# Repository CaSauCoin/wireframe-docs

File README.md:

# WireFrame EDA — User Guide

The WireFrame user guide: installation, tutorials, schematic, PCB layout, high-speed and power integrity, simulation, the AI Copilot, libraries, multi-board products, import/export, and reference pages. Published at **<https://wireframe.com.vn/docs/>** (the app's **Help → Documentation**).

This repository holds the **content** — Markdown, the media WireFrame records of itself, and the capture briefs. The pages are drawn by the website, [`wireframe-auth`](../wireframe-auth), with its own header, footer, theme and search (`app/docs_site.py`). Until October 2026 the guide was a separate MkDocs site; it is now one site with wireframe.com.vn, at the same URLs.

```mermaid
flowchart LR
    A[docs/**/*.md + guide.yml] -->|wireframe-auth/app/docs_site.py| B[Static pages at /docs/]
    C[doc_builder captures from the app] --> A
    B --> D[Cloudflare edge, with the website]
```

## Read it while you write it

From the `wireframe-auth` checkout next to this one:

```bash
python main.py                      # http://127.0.0.1:8000/docs/ — rendered on request from this repo
python scripts/build_docs.py build/docs-site --strict   # the static build the deploy makes; fails on a broken link
```

`WF_DOCS_DIR=/path/to/wireframe-docs` points the site at a checkout somewhere else. The deploy (`scripts/build_worker.py`) builds the guide on every Worker build.

## Layout

| Path | Purpose |
|---|---|
| `guide.yml` | The order of the guide (sections and pages) and the words on its home page |
| `docs/**/*.md` | The pages. A page's URL is its path: `docs/pcb/routing.md` → `/docs/pcb/routing/` |
| `docs/assets/wf/` | Screenshots and clips captured by WireFrame's `doc_builder` (with a manifest) |
| `docs/assets/app/` | Pictures drawn by the app's own lab tools (`wf-panel-shot`) — see `docs/assets/app/README.md` |
| `.wf-docs.yaml` | Per-scene settings for `doc_builder` (sample files, hints, skipped scenes) |
| `boards.yaml` | The real open-hardware boards the media is recorded on |
| `samples/` | Sample projects used by capture scenes |

## Writing a page

- Front matter: `description:` (the search snippet, 50–300 characters). Optional `status: new|beta`.
- Markdown with admonitions (`!!! note`), collapsible blocks (`??? question`), tabs (`=== "Tab"`), keys (`++ctrl+s++`), tables, definition lists and code blocks.
- Link pages by their relative `.md` path; the build turns them into URLs and fails on a missing one.
- Name the app's menus and buttons exactly as the app spells them. A page that promises a button the app does not have is worse than no page.
- Add the page to a section in `guide.yml`, or it is not published.

## Images and videos

Sections titled `### Image — …`, `### Short video — …` or `### Diagram — …` are capture slots. Each carries a brief (`!!! note "… brief"`) and, once captured, the media. The website hides the briefs and turns a captured slot into a figure; a slot without media is left out until it is captured. Capture with WireFrame's `doc_builder`:

```bash
python3 -m doc_builder docs-scan ../wireframe-docs
python3 -m doc_builder docs-fill ../wireframe-docs
```

Every picture is drawn by the app itself, on the boards in `boards.yaml` — never mocked up, never the 7805 test project.

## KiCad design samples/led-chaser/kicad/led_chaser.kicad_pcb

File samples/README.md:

# Sample data for documentation captures

Input files used when WireFrame's `doc_builder` lab captures the screenshots
and short videos in this guide (`python3 -m doc_builder docs-fill ../wireframe-docs`
from the WireFrame repository; see `.wf-docs.yaml`).

Everything here is **fictional** and made for this documentation — no
third-party data, no customer data. Regenerate with:

```bash
python3 samples/generate.py      # needs pdftoppm (poppler-utils) for the PNG
```

| File | What it is |
|---|---|
| `outlines/demo-board.dxf` | 80 × 60 mm board, R3 corners, four M3 holes 4 mm from each corner, a 20 × 12 mm battery pocket. ASCII DXF in millimetres |
| `outlines/demo-board.svg` | The same board as SVG (mm) |
| `datasheets/wf-demo8.pdf` | Two-page datasheet of **WF-DEMO8**, a fictional 8-pin SOIC-8 buck converter: pinout, operating conditions, application notes, package data |
| `datasheets/wf-demo8-pinout.png` | The pin table as an image, for the pin-OCR scene |
| `led-chaser/` | The [tutorial](../docs/tutorial/index.md) board — see below |

## The tutorial board: `led-chaser/`

An NE555 clock steps a 74HC4017 decade counter; its ten outputs light ten red
LEDs set in a ring, one at a time. 25 parts (0805 passives and LEDs, two SOIC
ICs, a 2-pin header, four M3 holes) on a 50 × 60 mm two-layer board. Fictional,
made for the tutorial, like everything else here.

| Folder | What it is | Made by |
|---|---|---|
| `kicad/` | The design input: schematic, part placement, the LED cathode ring and the outline, as a KiCad 8 project with its footprints beside it (`fp-lib-table`) | `python3 samples/led_chaser.py` |
| `1-schematic/` | WireFrame project, schematic only — where the tutorial's PCB section starts | WireFrame's KiCad importer, on `kicad/` without the `.kicad_pcb` |
| `2-placed/` | + the board: parts placed, cathode ring drawn, everything else ratsnest | WireFrame's KiCad importer, on `kicad/` |
| `3-routed/` | The finished board: `2-placed` after **Auto-route** in WireFrame, saved | WireFrame (Route Assist) |

`led_chaser.py` checks that the drawn wires make exactly the netlist in its
`PARTS` table before it writes anything. The symbols and footprints are copied
from the KiCad libraries (CC-BY-SA 4.0 with the libraries' design exception);
it reads them from `$KICAD_LIBS` (default `~/.wireframe/library_cache/repos`).

Rebuilding the WireFrame projects after a change to `led_chaser.py` or to the
importer, from the WireFrame repository:

```bash
python3 ../wireframe-docs/samples/led_chaser.py
S=../wireframe-docs/samples/led-chaser; T=$(mktemp -d)
mkdir -p $T/sch-in && cp -r $S/kicad/led_chaser.kicad_pro $S/kicad/led_chaser.kicad_sch $S/kicad/fp-lib-table $S/kicad/footprints $T/sch-in/
cmake-build-debug/tests/cpp/wf-import-kicad $T/sch-in/led_chaser.kicad_pro $T/sch
cmake-build-debug/tests/cpp/wf-import-kicad $S/kicad/led_chaser.kicad_pro $T/full
rm -rf $S/1-schematic $S/2-placed
cp -r $T/sch/led_chaser_WireFrame $S/1-schematic
cp -r $T/full/led_chaser_WireFrame $S/2-placed
```

Then open `2-placed/led_chaser.prjxml` in WireFrame, box-select the whole
board, press Ctrl+Shift+W (**Auto-route selection**), wait for the
notification, save, and copy the project's `.prjxml`, `.schxml`, `.pcbxml` and
`led_chaser_lib/` into `3-routed/` (not `ai_memory.db`). Check the result with
`cmake-build-debug/tests/cpp/wf-pcb-lab ../wireframe-docs/samples/led-chaser/3-routed --dfm`:
no ratsnest, **DFM & DRC 0 error(s), 0 warning(s)** (48 tracks and 25 vias with
the importer and router of 2026-11-02).

Some scenes generate their data at capture time with WireFrame's own labs
(`wf-enclosure-lab --make-demo`, `wf-assembly-lab --make-demo`) instead of
storing it here — see `prepare:` in `.wf-docs.yaml`.

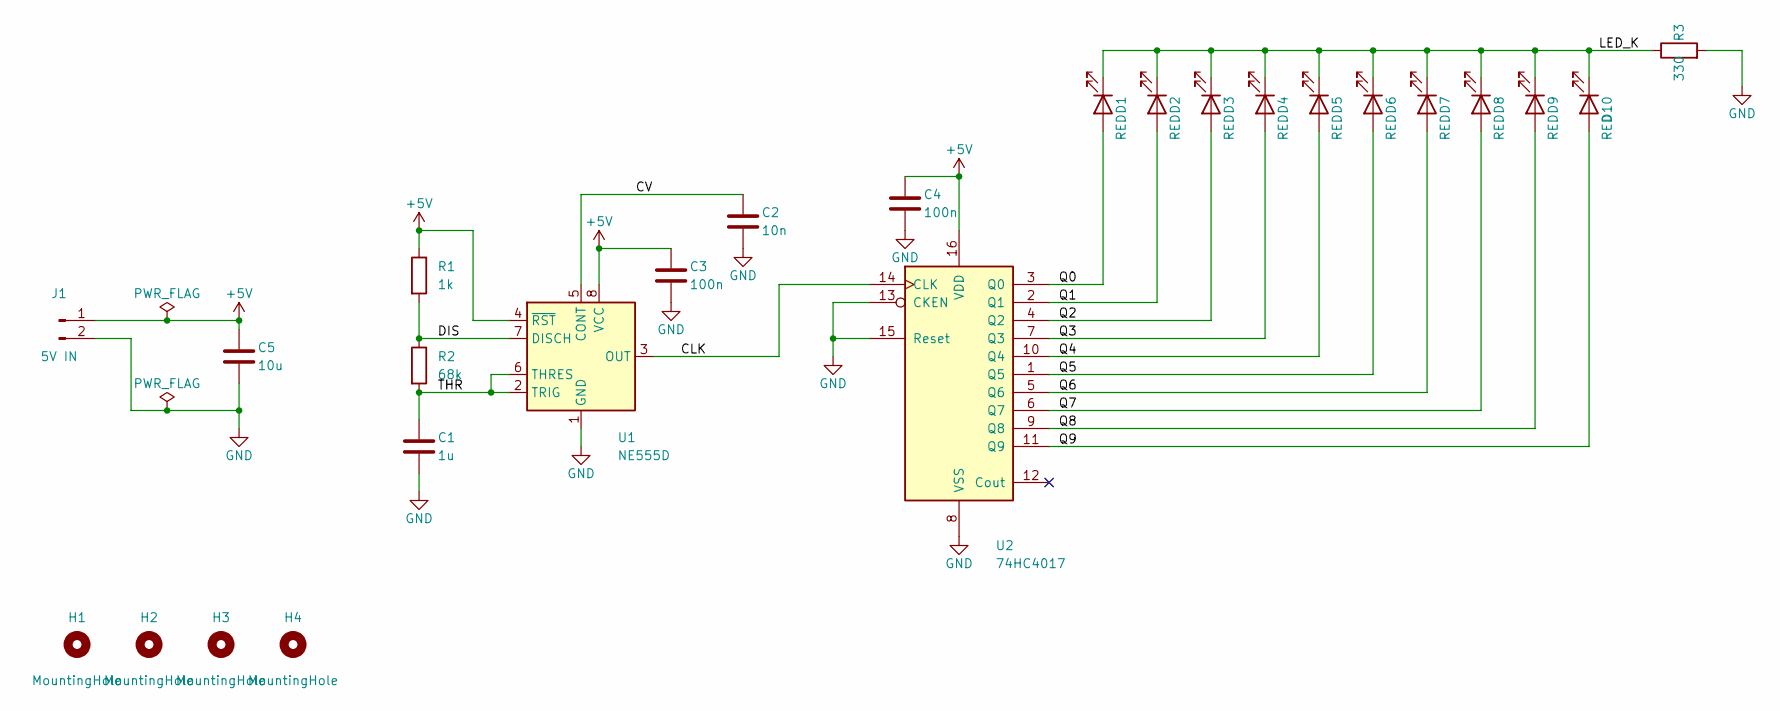
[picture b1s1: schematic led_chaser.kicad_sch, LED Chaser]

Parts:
C1: 1u; C_0805_2012Metric
C2: 10n; C_0805_2012Metric
C3, C4: 100n; C_0805_2012Metric
C5: 10u; C_0805_2012Metric
D1, D2, D3, D4, D5, D6, D7, D8, D9, D10: RED; LED_0805_2012Metric
H1, H2, H3, H4: MountingHole; MountingHole_3.2mm_M3
J1: 5V IN; PinHeader_1x02_P2.54mm_Vertical
R1: 1k; R_0805_2012Metric
R2: 68k; R_0805_2012Metric
R3: 330; R_0805_2012Metric
U1: NE555D; SOIC-8_3.9x4.9mm_P1.27mm
U2: 74HC4017; SOIC-16_3.9x9.9mm_P1.27mm

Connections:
+5V: C3.1, C4.1, C5.1, J1.1, R1.1, U1.4 (~RST), U1.8 (VCC), U2.16 (VDD)
CLK: U1.3 (OUT), U2.14 (CLK)
CV: C2.1, U1.5 (CONT)
DIS: R1.2, R2.1, U1.7 (DISCH)
GND: C1.2, C2.2, C3.2, C4.2, C5.2, J1.2, R3.2, U1.1 (GND), U2.8 (VSS), U2.13 (CKEN), U2.15 (Reset)
LED_K: D1.1 (K), D2.1 (K), D3.1 (K), D4.1 (K), D5.1 (K), D6.1 (K), D7.1 (K), D8.1 (K), D9.1 (K), D10.1 (K), R3.1
Q0: D1.2 (A), U2.3 (Q0)
Q1: D2.2 (A), U2.2 (Q1)
Q2: D3.2 (A), U2.4 (Q2)
Q3: D4.2 (A), U2.7 (Q3)
Q4: D5.2 (A), U2.10 (Q4)
Q5: D6.2 (A), U2.1 (Q5)
Q6: D7.2 (A), U2.5 (Q6)
Q7: D8.2 (A), U2.6 (Q7)
Q8: D9.2 (A), U2.9 (Q8)
Q9: D10.2 (A), U2.11 (Q9)
THR: C1.1, R2.2, U1.2 (TRIG), U1.6 (THRES)

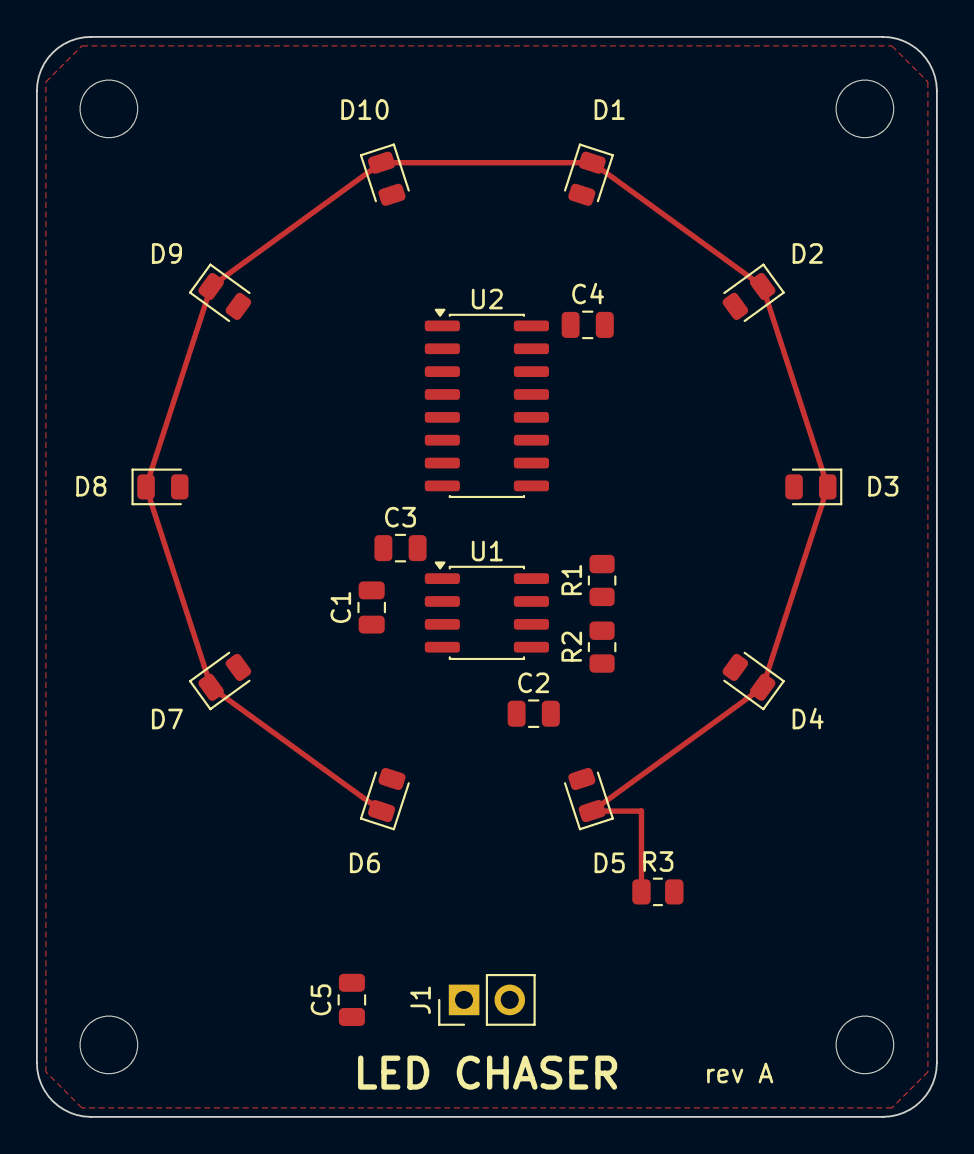
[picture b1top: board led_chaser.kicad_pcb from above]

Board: 2 copper layers, 50.0 x 60.0 mm, 25 parts (0 on the bottom side), 17 nets.

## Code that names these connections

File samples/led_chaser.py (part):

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    s.power("+5V", 76.2, 68.58)
    s.wire((76.2, 68.58), r1["1"])
    s.wire(r1["2"], r2["1"], u1["7"])                 # DIS: R1, R2, DISCH
    s.label("DIS", 78.74, 83.82)
    s.wire(r2["2"], c1["1"])                          # THR: R2, C1 ...
    s.wire(r2["2"], (86.36, 91.44), u1["2"])          # ... TRIG ...
    s.label("THR", 78.74, 91.44)
    s.wire(u1["6"], (86.36, 88.9), (86.36, 91.44))    # ... and THRES
    s.power("GND", 76.2, 105.41)
    s.wire(c1["2"], (76.2, 105.41))
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        s.wire(d["1"], (x, bus_y))
    r3 = s.place("R3", 254.0, bus_y, 90)
    s.wire(*[(x, bus_y) for x in cols], r3["1"])
    s.label("LED_K", 242.57, bus_y)
    s.wire(r3["2"], (262.89, bus_y), (262.89, 48.26))
    s.power("GND", 262.89, 48.26)

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
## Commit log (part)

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2026-02-09 Refactor UI & Docs
2026-02-09 Fix docs site_url
2026-03-25 Create Guide line
2026-03-25 add site on .ignore
2026-03-25 Trigger vercel deploy [skip ci]
2026-03-25 Deploy document guide line [skip ci]
2026-03-25 update mkdocs
2026-05-26 feat: initialize project structure and document third-party dependencies with license addition
